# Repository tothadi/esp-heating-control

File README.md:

# ESP Heating Control

An open-source, DIN-rail mounted controller for hydronic underfloor heating: 8 zone valve outputs, 2 pump outputs, a built-in OpenTherm master for the boiler, 8 floor NTC probe inputs, 8 dry-contact thermostat inputs, wired Ethernet (RJ45) and Wi-Fi, an 802.15.4 radio for Zigbee or Thread, an RTC, and a front panel with LEDs, an OLED and a button. It is built around an ESP32-S3 and runs either ESPHome (with Home Assistant as the user interface, and Zigbee sensors through the ESP32-H2) or a custom ESP-IDF firmware with a Thread border router and a Matter controller. It also works without Home Assistant.

| Closed, 230 V side | Closed, low-voltage side |
|---|---|
|  |  |

> **Status: design complete, not yet built.** Both PCBs are routed and pass DRC, and the enclosure passes a collision check against the 3D board models. Nothing has been manufactured or tested yet, and the firmware is written but untested. See [docs/open-issues.md](docs/open-issues.md).
>
> **Safety:** the lower board switches mains voltage (230 V AC). Build and install it only if you are qualified to work on mains wiring. The printed enclosure materials are not flame-rated (UL94 V-0), so the design is not suitable for sale as is.

## Features

* **Housing:** 10-module DIN-rail enclosure (175 × 90 mm), the usual circuit-breaker profile. 3D printed (SLA resin, with an MJF nylon DIN latch) with engraved terminal labels for hand painting, a printed spring latch for the DIN rail and printed light pipes.
* **Mains side:** 8 zone outputs (L + N each) for 230 V valve actuators and 2 pump outputs. 10 × Omron G5NB relays, HLK-5M05 power supply, fuse and varistor. 5.08 mm screw terminals rated 16 A / 300 V. At least 6.5 mm creepage/clearance between mains and low voltage.
* **Low-voltage side:** 8 floor NTC inputs (2 × ADS1115, 10 kΩ 0.1 % dividers, 10 µF filter capacitors), 8 dry-contact thermostat inputs (ESD-protected, 3.3 mA wetting current), a discrete OpenTherm master interface (24 V boost, current-limited line driver, polarity-independent), and 10/100 Ethernet (W5500 with an RJ45 jack). 3.5 mm screw terminals for the inputs and OpenTherm; the RJ45 ("LAN") sits at the right end of the same terminal row.
* **Logic board:** ESP32-S3-WROOM-1-N16R8 (16 MB flash, 8 MB octal PSRAM, Wi-Fi 4, BLE; module rated to 65 °C) plus an ESP32-H2-MINI-1 as 802.15.4 co-processor (Zigbee coordinator, or Thread radio for the S3's border router and Matter controller), wired Ethernet (W5500) on the power/IO board, DS3231M RTC with CR1220 backup, 0.91" 128 × 32 OLED, 11 status LEDs, one button, and a USB-C port per chip ("MAIN" for the S3, "RADIO" for the H2) for flashing and logging.
* **Connectivity:**
  * **Ethernet:** 10/100 through an RJ45 jack ("LAN", W5500).
  * **Wi-Fi:** 2.4 GHz Wi-Fi 4 on the ESP32-S3.
  * **ESPHome firmware:** both interfaces run by default, and Ethernet is used whenever the cable is plugged in and has a link. If the link drops, the controller falls back to Wi-Fi, and it returns to Ethernet when the cable is back. A switch turns Wi-Fi off for a wired-only setup; Ethernet-only and Wi-Fi-only builds are also available.
  * **Thread/Matter firmware:** the same choice is made at run time (`auto` / `ethernet` / `wifi`), and the active interface also carries the Thread border router's backbone.
  * **802.15.4 radio (ESP32-H2):** Zigbee or Thread devices.
  * **Bluetooth LE (S3):** Matter commissioning.
  * **Local control:** the controller keeps working without any network; only the dashboard, remote control and the clock sync need it, and the DS3231 RTC keeps the schedules running in between.
  * Details: [firmware/controller](firmware/controller/README.md#network-ethernet-andor-wi-fi), [firmware/thread-matter](firmware/thread-matter/README.md).
* **Manufacturing:** both boards are designed for single-side assembly and can be made by any PCB assembly service, JLCPCB for example. The Gerbers, BOM and CPL are included; the BOM/CPL files are in JLCPCB format and may need adapting for other services. The enclosure can be printed by any 3D printing service with SLA resin (and MJF nylon for the DIN latch and the OLED spacer), e.g. JLC3DP, which can also fit the threaded inserts. Hand work is limited to soldering the OLED module, fitting the window and final assembly.
* **Parametric:** the PCBs (KiCad) and the enclosure (CadQuery) are generated from Python scripts. The enclosure reads terminal and front-panel positions from the boards, so the two stay in sync.

## Repository layout

| Path | Contents |
|---|---|
| [docs/](docs) | Documentation (see below) |
| [hardware/pcb/lower/](hardware/pcb/lower) | Power/IO board (170 × 85 mm): KiCad project and terminal map; `fab/`: Gerbers, BOM/CPL (JLCPCB format) |
| [hardware/pcb/logic/](hardware/pcb/logic) | Logic board (165 × 40 mm): KiCad project and front-panel map; `fab/`: Gerbers, BOM/CPL (JLCPCB format) |
| [hardware/pcb/scripts/](hardware/pcb/scripts) | PCB generators and post-processing scripts |
| [hardware/pcb/components/](hardware/pcb/components) | Part library from LCSC/EasyEDA: `footprints.pretty/` (KiCad footprints) and `3d-models/` (STEP models) |
| [hardware/pcb/schematics/](hardware/pcb/schematics) | OpenTherm master interface schematic (SVG + generator) |
| [hardware/enclosure/models/](hardware/enclosure/models) | Enclosure parts: STL, STEP, OLED window DXF |
| [hardware/enclosure/drawings/](hardware/enclosure/drawings) | Threaded-insert drawing for the order |
| [hardware/enclosure/scripts/](hardware/enclosure/scripts) | CadQuery / VTK scripts |
| [hardware/enclosure/fonts/](hardware/enclosure/fonts) | Label font (Barlow Bold, SIL OFL) |
| [hardware/renders/](hardware/renders) | All images: board renders, assembly and enclosure views, shaded renders, label close-ups |
| [firmware/](firmware) | Controller firmware (all control runs on the controller): ESPHome + Zigbee co-processor, or ESP-IDF with Thread border router and Matter controller; the predecessor gateway's configuration for reference |
| [home-assistant/](home-assistant) | Home Assistant dashboard (the controller works without Home Assistant; HA is only dashboard and remote control) and optional notifications |

## Documentation

1. [Hardware: boards, pinout, OpenTherm interface](docs/hardware.md)
2. [Enclosure: dimensions, terminals, front panel, mounting, printing](docs/enclosure.md)
3. [Ordering and assembly](docs/assembly.md)
4. [Firmware and control logic](docs/firmware.md)
5. [Regenerating the design (build scripts)](docs/build-scripts.md)
6. [Open issues](docs/open-issues.md)

## Contributing

Contributions are welcome, especially reviews of the board designs and the circuitry before the first boards are built. See [CONTRIBUTING.md](CONTRIBUTING.md).

## Background

This controller grew out of a working home installation: an OpenTherm gateway (ESP32 + DIYLess OpenTherm Master Shield + 2 × ADS1115 on a custom PCB), a Zigbee 6-channel relay for the zone valves, Zigbee room thermostats and Home Assistant automations. It puts all of this into one DIN-rail device that can control the heating locally. The Home Assistant packages in [home-assistant/](home-assistant) are the reference implementation of the control logic, which the controller firmware will port to the ESP.

## Disclaimer

All designs, files and documentation in this repository are provided "as is", without warranty of any kind, express or implied. They have not been certified or tested for compliance with any safety or electrical standard. Anyone who builds, modifies, installs or uses them does so entirely at their own responsibility and risk.

The device switches 230 V mains. Mains wiring must be done only by a qualified person and in line with local regulations. The authors accept no liability for any damage, injury or loss resulting from the use of these designs.

## Next Steps

The project is currently in active development. Key next steps include:
- Completing the hardware design review and initial board fabrication.
- Add web UI with the features specified in the [web UI plan](docs/web-ui-plan.md).
- Implementing the firmware features as outlined in the [web UI plan](docs/web-ui-plan.md).
- Optional ceiling cooling for heat-pump systems, with humidity-based dew-point protection, as outlined in the
  [cooling plan](docs/cooling-plan.md).
- Testing the integration of the OpenTherm interface, Zigbee components, and the local control logic.
- Expanding the documentation to cover setup, usage, and troubleshooting.
- Gathering feedback from early adopters and contributors to refine both hardware and software.

## License

* Hardware (KiCad files, Gerbers, enclosure models and drawings): [CERN-OHL-S-2.0](LICENSES/CERN-OHL-S-2.0.txt)
* Software (Python scripts, ESPHome and Home Assistant configuration): [MIT](LICENSES/MIT.txt)
* Documentation and images: [CC BY-SA 4.0](LICENSES/CC-BY-SA-4.0.txt)

Third-party content keeps its own license: the Barlow font (SIL OFL 1.1, [hardware/enclosure/fonts/OFL.txt](hardware/enclosure/fonts/OFL.txt)), the KiCad standard library footprints and 3D models (CC BY-SA 4.0 with the KiCad library exception), and the LCSC/EasyEDA footprints and 3D models in [hardware/pcb/components/](hardware/pcb/components) (provided by LCSC, subject to their terms).

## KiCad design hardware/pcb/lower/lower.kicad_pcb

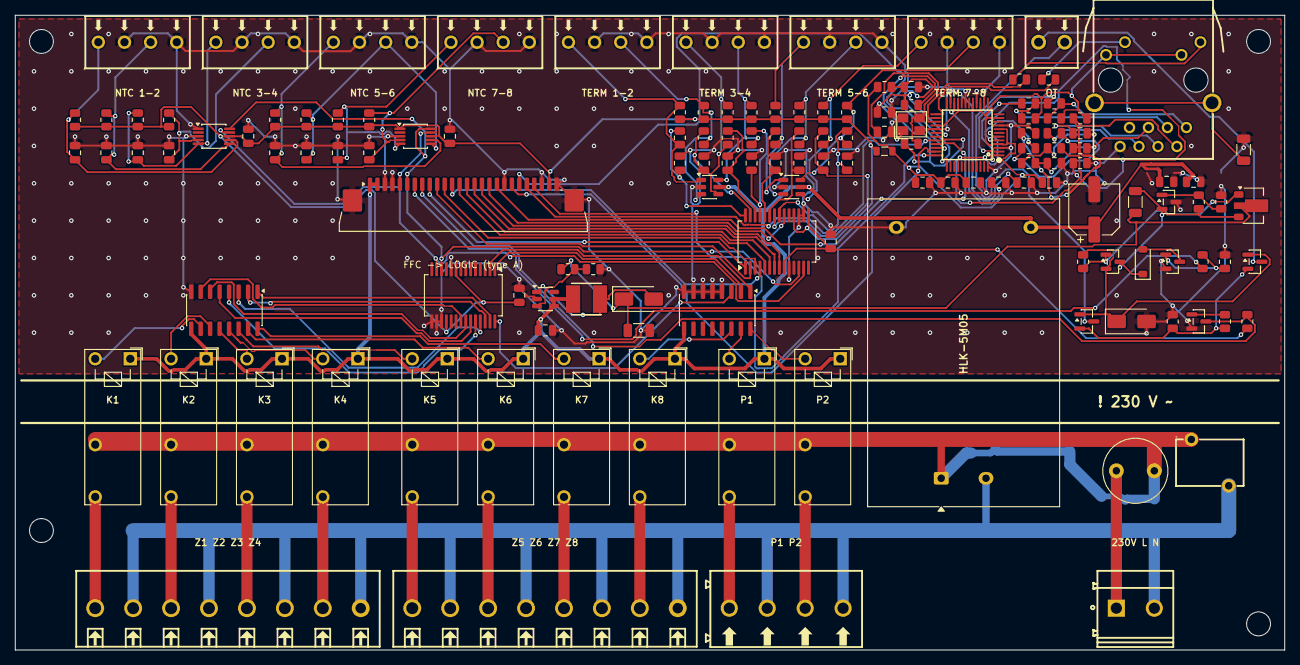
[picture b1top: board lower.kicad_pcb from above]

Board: 2 copper layers, 170.0 x 85.0 mm, 144 parts (0 on the bottom side), 116 nets.

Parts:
C1, C4, C11, C19, C29, C30, C31, C32, C33, C34, C35, C36, C37, C73, C77, C80, C81, C82: 100nF 50V X7R; C_0805_2012Metric
C10, C21, C22, C23, C24, C25, C26, C27, C28, C40, C85: 10uF 25V X5R; C_0805_2012Metric
C12: 220uF 16V 6.3x7.7 (RVT1C221M0607); CP_Elec_6.3x7.7
C41: 10uF 50V X5R 1206; C_1206_3216Metric
C70: 22nF X7R 50V; C_0805_2012Metric
C71, C72: 6.8nF X7R 50V; C_0805_2012Metric
C74: 1nF 2kV X7R 1206; C_1206_3216Metric
C75, C76: 18pF C0G 50V; C_0805_2012Metric
C83: 10nF X7R 50V; C_0805_2012Metric
C84: 4.7uF X5R 25V; C_0805_2012Metric
D20: SS34; D_SMA
D21: BZT52C4V3; D_SOD-123
D22, D23: BAT54S; SOT-23
D24: SMAJ24A; D_SMA
F1: T2A; Fuse_Littelfuse_372_D8.50mm
FB1: Ferrite 600R@100MHz 500mA; L_0805_2012Metric
H1, H2, H3, H4: MountingHole_3.2mm_M3
J1, J2, J3, J4, J5, J6, J7, J8: XY350V-3.5-4P screw terminal; CONN-TH_XY350V-3.5-4P
J9: XY350V-3.5-2P screw terminal; CONN-TH_XY350V-3.5-2P
J21, J22: DB128V-5.08-8P-GN-S screw terminal; CONN-TH_8P-P5.08_DB128V-5.08-8P-GN-S
J23: DB128V-5.08-4P-GN-S screw terminal; CONN-TH_4P-P5.08_DIBO_DB128V-5.08
J24: DB128V-5.08-2P-GN-S screw terminal; CONN-TH_2P-P5.08_DIBO_DB128V-5.08
J30: AFA07-S26FCA-00; JUSHUO_AFA07-S26FCA-00_1x26-1MP_P1.0mm_Horizontal
J40: J1B1211CCD RJ45 10/100 magjack; RJ45-TH_J1B1211CCD
K1, K2, K3, K4, K5, K6, K7, K8, K9, K10: G5NB-1A-E-DC5V; Relay_SPST_Omron_G5NB
L1: 22uH SWPA4030S220MT; IND-SMD_L4.0-W4.0_SLW4010S
PS1: HLK-5M05; Converter_ACDC_Hi-Link_HLK-5Mxx
Q1: BCX56-16,115 (Nexperia); SOT-89-3
Q2, Q3, Q4: MMBT3904; SOT-23
R21, R22, R23, R24, R25, R26, R27, R28: 10k 0.1%; R_0805_2012Metric
R30, R31, R32, R33, R34, R35, R36, R37, R40, R41, R42, R43, R44, R45, R46, R47, R56, R59: 1k 1%; R_0805_2012Metric
R50: 390k 1%; R_0805_2012Metric
R51, R54, R57, R84: 10k 1%; R_0805_2012Metric
R52: 2.2k 1% 1206; R_1206_3216Metric
R53: 68k 1%; R_0805_2012Metric
R55: 15R 1%; R_0805_2012Metric
R58: 47R 1%; R_0805_2012Metric
R60: 4.7k 1%; R_0805_2012Metric
R70, R71, R75, R76: 3.3R 1%; R_0805_2012Metric
R72, R73, R77, R78: 49.9R 1%; R_0805_2012Metric
R74: 10R 1%; R_0805_2012Metric
R79: 12.4k 1%; R_0805_2012Metric
R80, R81: 470R 1%; R_0805_2012Metric
R82: 1M 1%; R_0805_2012Metric
R83: 0R; R_0805_2012Metric
RV1: 07D471K; RES-TH_L9.0-W6.2-P5.00-D0.7-S6.20
U1, U14: MCP23017-E/SS; SSOP-28_5.3x10.2mm_P0.65mm
U2, U3: ULN2003A; SOIC-16_3.9x9.9mm_P1.27mm
U10, U11: ADS1115IDGSR; MSOP-10_3x3mm_P0.5mm
U12, U13: SRV05-4; SOT-23-6
U20: MT3608; SOT-23-6
U21: CJ431; SOT-23
U30: W5500; LQFP-48_L7.0-W7.0-P0.50-LS9.0-BL
Y30: 25MHz 12pF X322525MOB4SI; CRYSTAL-SMD_4P-L3.2-W2.5-BL

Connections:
+3V3: C1.1, C4.1, C19.1, C29.1, FB1.1, J30.25, R21.1, R22.1, R23.1, R24.1, R25.1, R26.1, R27.1, R28.1, R30.1, R31.1, R32.1, R33.1, R34.1, R35.1, R36.1, R37.1, R60.1, U1.9, U1.18, U10.8, U11.1, U11.8, U14.9, U14.15, U14.18
+3V3E: C80.1, C81.1, C82.1, C85.1, FB1.2, J40.10, J40.12, R72.2, R73.2, R74.2, R84.1, U30.4, U30.8, U30.11, U30.15, U30.17, U30.21, U30.28
+5V: C10.1, C11.1, C12.1, C40.1, J30.1, J30.2, K1.A1, K2.A1, K3.A1, K4.A1, K5.A1, K6.A1, K7.A1, K8.A1, K9.A1, K10.A1, L1.1, PS1.4, U2.9, U3.9, U12.5, U13.5, U20.4, U20.5
+24V: C41.1, D20.1, Q1.2, R50.1, R52.1
CHGND: C74.1, J40.13, J40.14
COIL1: K1.A2, U2.10
COIL2: K2.A2, U2.11
COIL3: K3.A2, U2.12
COIL4: K4.A2, U2.13
COIL5: K5.A2, U2.14
COIL6: K6.A2, U2.15
COIL7: K7.A2, U2.16
COIL8: K8.A2, U3.14
COIL9: K9.A2, U3.15
COIL10: K10.A2, U3.16
ETH_1V2O: C83.1, U30.22
ETH_ACT: R81.2, U30.27
ETH_CS: J30.22, U30.32
ETH_EXRES: R79.1, U30.10
ETH_GLEDK: J40.9, R81.1
ETH_INT: J30.23, U30.36
ETH_LINK: R80.2, U30.25
ETH_MISO: J30.21, U30.34
ETH_MOSI: J30.20, U30.35
ETH_RDN: C71.1, J40.6
ETH_RDP: C72.1, J40.4
ETH_RST: C77.1, R84.2, U30.37
ETH_RXCM: C73.1, J40.5, R77.2, R78.2
ETH_RXN: R75.2, U30.5
ETH_RXN_M: C71.2, R75.1, R77.1
ETH_RXP: R76.2, U30.6
ETH_RXP_M: C72.2, R76.1, R78.1
ETH_SCK: J30.18, U30.33
ETH_TCT: C70.1, J40.2, R74.1
ETH_TDN: J40.3, R70.2, R72.1
ETH_TDP: J40.1, R71.2, R73.1
ETH_TOCAP: C84.1, U30.20
ETH_TXN: R70.1, U30.1
ETH_TXP: R71.1, U30.2
ETH_XI: C75.1, R82.1, U30.30, Y30.1
ETH_XO: R82.2, R83.1, U30.31
ETH_XO2: C76.1, R83.2, Y30.3
ETH_YLEDK: J40.11, R80.1
FB: R50.2, R51.1, U20.3
GND: C1.2, C4.2, C10.2, C11.2, C12.2, C19.2, C21.2, C22.2, C23.2, C24.2, C25.2, C26.2, C27.2, C28.2, C29.2, C30.2, C31.2, C32.2, C33.2, C34.2, C35.2, C36.2, C37.2, C40.2, C41.2, C70.2, C73.2, C74.2, C75.2, C76.2, C77.2, C80.2, C81.2, C82.2, C83.2, C84.2, C85.2, D24.2, J1.2, J1.4, J2.2, J2.4, J3.2, J3.4, J4.2, J4.4, J5.2, J5.4, J6.2, J6.4, J7.2, J7.4, J8.2, J8.4, J30.3, J30.4, J30.19, J30.24, J30.26, J30.MP, J40.8, PS1.3, Q3.2, Q4.2, R51.2, R54.2, R57.2, R58.2, R79.2, U1.10, U1.15, U1.16, U1.17, U2.8, U3.4, U3.5, U3.6, U3.7, U3.8, U10.1, U10.3, U11.3, U12.2, U13.2, U14.10, U14.16, U14.17, U20.2, U21.3, U30.3, U30.9, U30.14, U30.16, U30.19, U30.23, U30.29, U30.48, Y30.2, Y30.4
LEDZ1: J30.9, U14.1
LEDZ2: J30.10, U14.2
LEDZ3: J30.11, U14.3
LEDZ4: J30.12, U14.4
LEDZ5: J30.13, U14.5
LEDZ6: J30.14, U14.6
LEDZ7: J30.15, U14.7
LEDZ8: J30.16, U14.8
LOUT1: J21.1, K1.14
LOUT2: J21.3, K2.14
LOUT3: J21.5, K3.14
LOUT4: J21.7, K4.14
LOUT5: J22.1, K5.14
LOUT6: J22.3, K6.14
LOUT7: J22.5, K7.14
LOUT8: J22.7, K8.14
LOUT9: J23.1, K9.14
LOUT10: J23.3, K10.14
L_F: F1.2, K1.13, K2.13, K3.13, K4.13, K5.13, K6.13, K7.13, K8.13, K9.13, K10.13, PS1.1, RV1.1
L_IN: F1.1, J24.1
MCP_INT: J30.17, U14.20
NTC1: C21.1, J1.1, R21.2, U10.7
NTC2: C22.1, J1.3, R22.2, U10.6
NTC3: C23.1, J2.1, R23.2, U10.5
NTC4: C24.1, J2.3, R24.2, U10.4
NTC5: C25.1, J3.1, R25.2, U11.7
NTC6: C26.1, J3.3, R26.2, U11.6
NTC7: C27.1, J4.1, R27.2, U11.5
NTC8: C28.1, J4.3, R28.2, U11.4
N_AC: J21.2, J21.4, J21.6, J21.8, J22.2, J22.4, J22.6, J22.8, J23.2, J23.4, J24.2, PS1.2, RV1.2
OT_A: D22.3, J9.1
OT_B: D23.3, J9.2
OT_BASE: D21.1, Q1.3, Q2.3, R52.2, R53.1, U21.2
OT_E: Q1.1, Q2.1, R55.1
OT_LINE: D22.1, D23.1, D24.1, Q2.2, R55.2
OT_LOW: D21.2, Q3.3
OT_REF: R53.2, R54.1, U21.1
OT_RET: D22.2, D23.2, R58.1, R59.1
OT_RX: J30.8, Q4.3, R60.2
OT_RXB: Q4.1, R59.2
OT_TX: J30.7, R56.1
OT_TXB: Q3.1, R56.2, R57.1
RIN1: U1.21, U2.7
RIN2: U1.22, U2.6
RIN3: U1.23, U2.5
RIN4: U1.24, U2.4
RIN5: U1.25, U2.3
RIN6: U1.26, U2.2
RIN7: U1.27, U2.1
RIN8: U1.28, U3.3
RIN9: U1.1, U3.2
RIN10: U1.2, U3.1
SCL: J30.6, U1.12, U10.10, U11.10, U14.12
SDA: J30.5, U1.13, U10.9, U11.9, U14.13
SW_BOOST: D20.2, L1.2, U20.1
TIN1: J5.1, R30.2, R40.1, U12.1
TIN2: J5.3, R31.2, R41.1, U12.3
TIN3: J6.1, R32.2, R42.1, U12.4
TIN4: J6.3, R33.2, R43.1, U12.6
TIN5: J7.1, R34.2, R44.1, U13.1
TIN6: J7.3, R35.2, R45.1, U13.3
TIN7: J8.1, R36.2, R46.1, U13.4
TIN8: J8.3, R37.2, R47.1, U13.6
TINF1: C30.1, R40.2, U14.28
TINF2: C31.1, R41.2, U14.27
TINF3: C32.1, R42.2, U14.26
TINF4: C33.1, R43.2, U14.25
TINF5: C34.1, R44.2, U14.24
TINF6: C35.1, R45.2, U14.23
TINF7: C36.1, R46.2, U14.22
TINF8: C37.1, R47.2, U14.21

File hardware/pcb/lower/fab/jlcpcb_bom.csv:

Comment,Designator,Footprint,LCSC Part #
100nF 50V X7R,"C1,C4,C11,C19,C29,C30,C31,C32,C33,C34,C35,C36,C37,C73,C77,C80,C81,C82",C_0805_2012Metric,C49678
10uF 25V X5R,"C10,C21,C22,C23,C24,C25,C26,C27,C28,C40,C85",C_0805_2012Metric,C15850
220uF 16V 6.3x7.7 (RVT1C221M0607),C12,CP_Elec_6.3x7.7,C970695
10uF 50V X5R 1206,C41,C_1206,C13585
22nF X7R 50V,C70,C_0805,C1729
6.8nF X7R 50V,"C71,C72",C_0805,C1755
1nF 2kV X7R 1206,C74,C_1206,C9196
18pF C0G 50V,"C75,C76",C_0805,C1797
10nF X7R 50V,C83,C_0805,C1710
4.7uF X5R 25V,C84,C_0805,C1779
SS34,D20,D_SMA,C8678
BZT52C4V3,D21,SOD-123,C19077399
BAT54S,"D22,D23",SOT-23,C7420333
SMAJ24A,D24,D_SMA,C19077541
T2A 250V TR5 (2010T2A250V),F1,Fuse_Littelfuse_372_D8.50mm,C354902
Ferrite 600R@100MHz 500mA,FB1,0805,C1017
XY350V-3.5-4P screw terminal,"J1,J2,J3,J4,J5,J6,J7,J8",XY350V-3.5-4P,C557656
XY350V-3.5-2P screw terminal,J9,XY350V-3.5-2P,C784942
DB128V-5.08-8P-GN-S screw terminal,"J21,J22",DB128V-5.08-8P,C5143711
DB128V-5.08-4P-GN-S screw terminal,J23,DB128V-5.08-4P,C2915641
DB128V-5.08-2P-GN-S screw terminal,J24,DB128V-5.08-2P,C2915639
AFA07-S26FCA-00 FFC 26P 1.0mm,J30,JUSHUO_AFA07-S26FCA-00,C2681942
J1B1211CCD RJ45 10/100 magjack,J40,RJ45-TH_J1B1211CCD,C910371
G5NB-1A-E-DC5V,"K1,K2,K3,K4,K5,K6,K7,K8,K9,K10",Relay_SPST_Omron_G5NB,C48746
22uH SWPA4030S220MT,L1,4x4,C83472
HLK-5M05,PS1,Converter_ACDC_Hi-Link_HLK-5Mxx,C209907
"BCX56-16,115 (Nexperia)",Q1,SOT-89,C100026
MMBT3904,"Q2,Q3,Q4",SOT-23,C20526
10k 0.1%,"R21,R22,R23,R24,R25,R26,R27,R28",R_0805,C110775
1k 1%,"R30,R31,R32,R33,R34,R35,R36,R37,R40,R41,R42,R43,R44,R45,R46,R47,R56,R59",R_0805,C17513
390k 1%,R50,R_0805,C17656
10k 1%,"R51,R54,R57,R84",R_0805,C17414
2.2k 1% 1206,R52,R_1206,C17948
68k 1%,R53,R_0805,C17801
15R 1%,R55,R_0805,C17480
47R 1%,R58,R_0805,C17714
4.7k 1%,R60,R_0805,C17673
3.3R 1%,"R70,R71,R75,R76",R_0805,C2907250
49.9R 1%,"R72,R73,R77,R78",R_0805,C17720
10R 1%,R74,R_0805,C17415
12.4k 1%,R79,R_0805,C30908
470R 1%,"R80,R81",R_0805,C17710
1M 1%,R82,R_0805,C17514
0R,R83,R_0805,C17477
07D471K,RV1,RES-TH_L9.0-W6.2-P5.00-D0.7-S6.20,C28756
MCP23017-E/SS,"U1,U14",SSOP-28_5.3x10.2mm_P0.65mm,C506653
ULN2003A,"U2,U3",SOIC-16_3.9x9.9mm_P1.27mm,C688859
ADS1115IDGSR,"U10,U11",MSOP-10,C37593
SRV05-4,"U12,U13",SOT-23-6,C13612
MT3608,U20,SOT-23-6,C84817
CJ431,U21,SOT-23,C3113
W5500,U30,LQFP-48,C32843
25MHz 12pF X322525MOB4SI,Y30,3225,C9006

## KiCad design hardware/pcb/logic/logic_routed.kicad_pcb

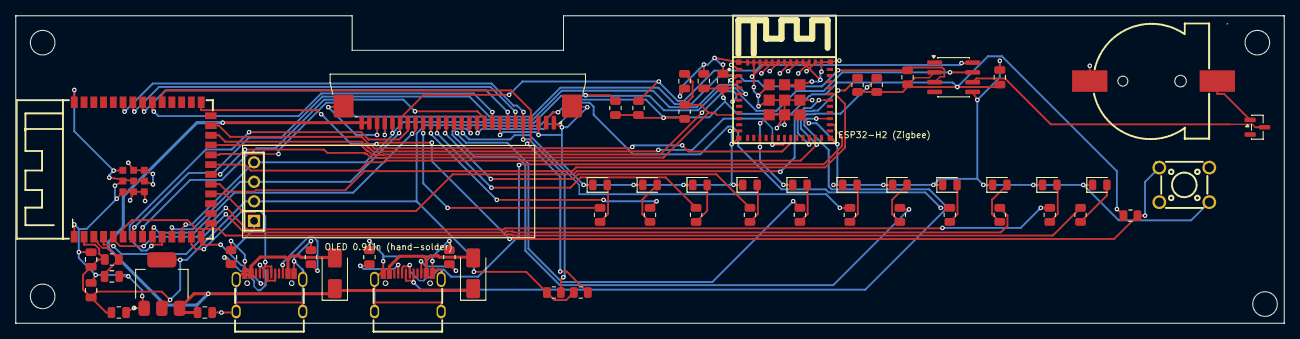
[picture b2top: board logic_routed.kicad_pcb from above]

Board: 2 copper layers, 165.0 x 40.0 mm, 62 parts (0 on the bottom side), 59 nets.

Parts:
BT1: BS-12-B2AA002 (CR1220); BAT-SMD_BS-12-B2AA002
C40, C41, C48: 10uF 25V X5R; C_0805_2012Metric
C43, C45, C49: 100nF 50V X7R; C_0805_2012Metric
C44, C50: 1uF 50V X7R; C_0805_2012Metric
C47: 22uF 25V X5R; C_0805_2012Metric
D1, D2: SS34; D_SMA
D14: BAT54S; SOT-23
D20, D21, D22, D23, D24, D25, D26, D27: LED green 0805; LED_0805_2012Metric
D28, D29: LED yellow 0805; LED_0805_2012Metric
D30: LED red 0805; LED_0805_2012Metric
H1, H2, H3, H4: MountingHole_3.2mm_M3
J1: AFA07-S26FCA-00; JUSHUO_AFA07-S26FCA-00_1x26-1MP_P1.0mm_Horizontal
J2, J4: TYPE-C-31-M-12; USB-C_SMD-TYPE-C-31-M-12_1
J3: PZ254V-11-04P pin header 1x4 2.54mm (OLED); HDR-TH_4P-P2.54-V-M
R9, R10, R28, R29: 4.7k 1%; R_0805_2012Metric
R17, R19, R20, R25, R26, R27: 10k 1%; R_0805_2012Metric
R21, R22, R23, R24: 5.1k 1%; R_0805_2012Metric
R50, R51, R52, R53, R54, R55, R56, R57, R58, R59, R60: 330R 1%; R_0805_2012Metric
SW1: KH-6X6X13H-TJ; SW-TH_4P-L6.0-W6.0-P4.50-LS6.5
U1: ESP32-S3-WROOM-1-N16R8; WIRELM-SMD_ESP32-S3-WROOM-1
U2: AMS1117-3.3; SOT-223-3_TabPin2
U6: DS3231MZ+TRL; SOIC-8_3.9x4.9mm_P1.27mm
U7: ESP32-H2-MINI-1-H4S; WIRELM-SMD_ESP32-H2-MINI-1-H4

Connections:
+3V3: C41.1, C43.1, C45.1, C47.1, C48.1, C49.1, J1.2, J3.2, R9.1, R10.1, R17.1, R19.1, R20.1, R25.1, R26.1, R27.1, R28.1, R29.1, U1.2, U2.2, U6.2, U7.3
+5V: C40.1, D1.1, D2.1, J1.25, J1.26, U2.3
BATP: BT1.1, D14.1
BTN: R19.2, SW1.1, U1.27
CC1: J2.A5, R21.1
CC2: J2.B5, R22.1
CC3: J4.A5, R23.1
CC4: J4.B5, R24.1
EN: C44.1, R17.2, U1.3
ETH_CS: J1.5, R28.2, U1.35
ETH_INT: J1.4, R29.2, U1.31
ETH_MISO: J1.6, U1.34
ETH_MOSI: J1.7, U1.33
ETH_SCK: J1.9, U1.32
GND: BT1.2, C40.2, C41.2, C43.2, C44.2, C45.2, C47.2, C48.2, C49.2, C50.1, D20.1, D21.1, D22.1, D23.1, D24.1, D25.1, D26.1, D27.1, D28.1, D29.1, D30.1, J1.1, J1.3, J1.8, J1.23, J1.24, J1.MP, J2.1, J2.2, J2.3, J2.4, J2.A1B12, J2.B1A12, J3.1, J4.1, J4.2, J4.3, J4.4, J4.A1B12, J4.B1A12, R21.2, R22.2, R23.2, R24.2, SW1.4, U1.1, U1.40, U1.41, U2.1, U6.5, U7.1, U7.2, U7.11, U7.14, U7.36, U7.37, U7.38, U7.39, U7.40, U7.41, U7.42, U7.43, U7.44, U7.45, U7.46, U7.47, U7.48, U7.49, U7.50, U7.51, U7.52, U7.53
H2_BOOT: R27.2, U1.21, U7.23
H2_EN: C50.2, R25.2, U1.20, U7.8
H2_IO8: R26.2, U7.22
H2_RXD: U1.18, U7.30
H2_TXD: U1.19, U7.31
LEDA1: D20.2, R50.1
LEDA2: D21.2, R51.1
LEDA3: D22.2, R52.1
LEDA4: D23.2, R53.1
LEDA5: D24.2, R54.1
LEDA6: D25.2, R55.1
LEDA7: D26.2, R56.1
LEDA8: D27.2, R57.1
LEDA9: D28.2, R58.1
LEDA10: D29.2, R59.1
LEDA11: D30.2, R60.1
LEDZ1: J1.18, R50.2
LEDZ2: J1.17, R51.2
LEDZ3: J1.16, R52.2
LEDZ4: J1.15, R53.2
LEDZ5: J1.14, R54.2
LEDZ6: J1.13, R55.2
LEDZ7: J1.12, R56.2
LEDZ8: J1.11, R57.2
LED_P1: R58.2, U1.4
LED_P2: R59.2, U1.5
LED_ST: R60.2, U1.6
MCP_INT: J1.10, U1.8
OT_RX: J1.19, U1.9
OT_TX: J1.20, U1.10
PTA1: U1.22, U7.5
PTA2: U1.23, U7.6
PTA3: U1.24, U7.18
PTA4: U1.25, U7.19
RTC_INT: R20.2, U1.7, U6.3
SCL: J1.21, J3.3, R10.2, U1.11, U6.8
SDA: J1.22, J3.4, R9.2, U1.12, U6.7
USB2_DN: J4.A7, J4.B7, U7.26
USB2_DP: J4.A6, J4.B6, U7.27
USB_DN: J2.A7, J2.B7, U1.13
USB_DP: J2.A6, J2.B6, U1.14
VBAT: D14.3, U6.6
VBUS: D1.2, J2.A4B9, J2.B4A9
VBUS2: D2.2, J4.A4B9, J4.B4A9

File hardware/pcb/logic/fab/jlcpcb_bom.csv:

Comment,Designator,Footprint,LCSC Part #
BS-12-B2AA002 (CR1220),BT1,BS-12,C964721
10uF 25V X5R,"C40,C41,C48",C_0805,C15850
100nF 50V X7R,"C43,C45,C49",C_0805,C49678
1uF 50V X7R,"C44,C50",C_0805,C28323
22uF 25V X5R,C47,C_0805,C45783
SS34,"D1,D2",D_SMA,C8678
BAT54S,D14,SOT-23,C7420333
LED green 0805,"D20,D21,D22,D23,D24,D25,D26,D27",LED_0805,C2297
LED yellow 0805,"D28,D29",LED_0805,C2296
LED red 0805,D30,LED_0805,C84256
AFA07-S26FCA-00 FFC 26P 1.0mm,J1,JUSHUO_AFA07-S26FCA-00,C2681942
TYPE-C-31-M-12,"J2,J4",USB-C-16P,C165948
PZ254V-11-04P pin header 1x4 2.54mm (OLED),J3,HDR-1x4-P2.54-V,C492403
4.7k 1%,"R9,R10,R28,R29",R_0805,C17673
10k 1%,"R17,R19,R20,R25,R26,R27",R_0805,C17414
5.1k 1%,"R21,R22,R23,R24",R_0805,C27834
330R 1%,"R50,R51,R52,R53,R54,R55,R56,R57,R58,R59,R60",R_0805,C17630
KH-6X6X13H-TJ,SW1,6x6 H13,C2837523
ESP32-S3-WROOM-1-N16R8,U1,ESP32-S3-WROOM-1,C2913202
AMS1117-3.3,U2,SOT-223,C6186
DS3231MZ+TRL,U6,SOIC-8,C107410
ESP32-H2-MINI-1-H4S,U7,ESP32-H2-MINI-1,C47967030

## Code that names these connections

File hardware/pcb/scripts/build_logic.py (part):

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# 30 RXD0 (GPIO23), 31 TXD0 (GPIO24). The S3 drives EN and BOOT (IO12/IO13), so it can reset the H2 or flash it (e.g. the Thread RCP image) over the UART.
H2_XY = (100.0, 10.98)                # footprint origin; the module spans y 0 .. 16.6 (antenna y 0 .. 5.14 at the board edge)
h2pins = {n: "GND" for n in (1, 2, 11, 14, *range(36, 54))}
h2pins.update({3: "+3V3", 8: "H2_EN", 22: "H2_IO8", 23: "H2_BOOT", 26: "USB2_DN", 27: "USB2_DP", 30: "H2_RXD", 31: "H2_TXD",
               5: "PTA1", 6: "PTA2", 18: "PTA3", 19: "PTA4"})      # IO2, IO3, IO4, IO5: coexistence lines to the S3
part("lcsc", "WIRELM-SMD_ESP32-H2-MINI-1-H4", "U7", "H2", H2_XY, 0, h2pins)
g.area([(H2_XY[0] - 8.6, 0.2), (H2_XY[0] + 8.6, 0.2), (H2_XY[0] + 8.6, 5.3), (H2_XY[0] - 8.6, 5.3)], "ANT2")   # antenna: y 0 .. 5.14
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
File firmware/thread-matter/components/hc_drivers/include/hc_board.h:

#pragma once
// ESP Heating Control - logic board pin map (ESP32-S3-WROOM-1-N16R8). Source: hardware/build_logic.py.
#include "driver/gpio.h"

// Front panel
#define HC_PIN_BUTTON        GPIO_NUM_0    // BOOT strap, 10 kOhm pull-up, pressed = low
#define HC_PIN_LED_PUMP1     GPIO_NUM_4
#define HC_PIN_LED_PUMP2     GPIO_NUM_5
#define HC_PIN_LED_STATUS    GPIO_NUM_6
// I2C: MCP23017 0x20/0x21, ADS1115 0x48/0x49 (power/IO board, via the FFC), SSD1306 0x3C, DS3231M 0x68
#define HC_PIN_I2C_SDA       GPIO_NUM_8
#define HC_PIN_I2C_SCL       GPIO_NUM_18
#define HC_PIN_RTC_INT       GPIO_NUM_7    // DS3231 INT/SQW (unused)
#define HC_PIN_MCP_INT       GPIO_NUM_15   // MCP23017 INT (unused: inputs are polled)
// OpenTherm master interface (power/IO board). TX high = line idle; RX low = boiler current high (inverted).
#define HC_PIN_OT_TX         GPIO_NUM_17
#define HC_PIN_OT_RX         GPIO_NUM_16
// ESP32-H2 co-processor
#define HC_PIN_H2_TX         GPIO_NUM_10   // S3 TX -> H2 RXD0 (GPIO23)
#define HC_PIN_H2_RX         GPIO_NUM_11   // S3 RX <- H2 TXD0 (GPIO24)
#define HC_PIN_H2_EN         GPIO_NUM_12   // H2 EN (10 kOhm pull-up, 1 uF)
#define HC_PIN_H2_BOOT       GPIO_NUM_13   // H2 GPIO9 (10 kOhm pull-up)
// Wi-Fi / 802.15.4 coexistence (PTA), S3 = leader, H2 = follower
#define HC_PIN_PTA_REQUEST   GPIO_NUM_14   // <- H2 GPIO2
#define HC_PIN_PTA_PRIORITY  GPIO_NUM_21   // <- H2 GPIO3
#define HC_PIN_PTA_GRANT     GPIO_NUM_47   // -> H2 GPIO4
#define HC_PIN_PTA_TX_LINE   GPIO_NUM_48   // -> H2 GPIO5
// W5500 Ethernet (power/IO board, via the FFC); no reset line
#define HC_PIN_ETH_INT       GPIO_NUM_38
#define HC_PIN_ETH_SCK       GPIO_NUM_39
#define HC_PIN_ETH_MOSI      GPIO_NUM_40
#define HC_PIN_ETH_MISO      GPIO_NUM_41
#define HC_PIN_ETH_CS        GPIO_NUM_42

#define HC_ADDR_MCP_RELAYS   0x20   // GPA0..7 = Z1..Z8, GPB0..1 = P1..P2 (through ULN2003A)
#define HC_ADDR_MCP_IO       0x21   // GPA0..7 = TERM8..TERM1, GPB0..7 = zone LED 1..8
#define HC_ADDR_ADS_A        0x48   // AIN3..AIN0 = NTC1..NTC4
#define HC_ADDR_ADS_B        0x49   // AIN3..AIN0 = NTC5..NTC8
#define HC_ADDR_OLED         0x3C
#define HC_ADDR_RTC          0x68

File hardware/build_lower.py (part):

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                 value=P["RELAY"][0], anchor="A1", part=P["RELAY"])
    g.pin(fp, "A1", "+5V")
    g.pin(fp, "A2", f"COIL{k}")
    g.pin(fp, "13", "L_F")
    g.pin(fp, "14", f"LOUT{k}")
    g.silk(f"K{k}" if k <= 8 else f"P{k - 8}", (RELAY_X[k] - 2.35, RELAY_Y + 5.5), 0.9, bold=True)

# --- HLK-5M05 vertical, spanning the band: AC below (230 V), DC above (SELV) ----------------------------
HLK_AC1 = (124.0, 62.0)            # 90°: AC1 (124, 62), AC2 (130, 62), -Vo (118, 28.4), +Vo (136, 28.4)
fp = g.place("Converter_ACDC", "Converter_ACDC_Hi-Link_HLK-5Mxx", "PS1", HLK_AC1, rot=90, value="HLK-5M05", anchor="1", part=P["HLK"])
g.pin(fp, 1, "L_F")
g.pin(fp, 2, "N_AC")
g.pin(fp, 3, "GND")
g.pin(fp, 4, "+5V")
g.silk("HLK-5M05", (127.0, 44.0), 1.0, bold=True, rot=90)
FUSE1, FUSE2 = (L_IN_X, 61.0), (L_IN_X + 5.08, 61.0)
fp = g.place("Fuse", "Fuse_Littelfuse_372_D8.50mm", "F1", FUSE1, value="T2A", anchor="1", part=P["FUSE"])
g.pin(fp, 1, "L_IN")
g.pin(fp, 2, "L_F")
VAR1, VAR2 = (157.5, 56.8), (162.5, 56.8)
fp = g.place("Capacitor_THT", "C_Disc_D7.0mm_W2.5mm_P5.00mm", "RV1", VAR1, value="07D471K", anchor="1", part=P["MOV"])
g.pin(fp, 1, "L_F")
g.pin(fp, 2, "N_AC")
for ref, xy, key, rot in (("C10", (119.0, 19.5), "C10u", 90), ("C11", (135.0, 19.5), "C100n", 90), ("C12", (127.0, 19.5), "C220u", 0)):
    lib, name = ("Capacitor_SMD", P[key][1])
    fp = g.place(lib, name, ref, xy, rot=rot, value=P[key][0], part=P[key])
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part("Package_TO_SOT_SMD", "SOT-23-6", "U20", "MT3608", (145.0, 15.0), 0, {1: "SW_BOOST", 2: "GND", 3: "FB", 4: "+5V", 5: "+5V"})
fp = g.place("lcsc", "IND-SMD_L4.0-W4.0_SLW4010S", "L1", (151.0, 15.0), value=P["L22u"][0], part=P["L22u"])
g.pin(fp, 1, "+5V")
g.pin(fp, 2, "SW_BOOST")
part("Diode_SMD", "D_SMA", "D20", "SS34", (159.0, 15.0), 0, {1: "+24V", 2: "SW_BOOST"})
two("C40", "C10u", (145.0, 19.6), "+5V", "GND", rot=0)
two("C41", "C10u50", (159.0, 19.6), "+24V", "GND", rot=0, fpkind=("Capacitor_SMD", "C_1206_3216Metric"))
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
